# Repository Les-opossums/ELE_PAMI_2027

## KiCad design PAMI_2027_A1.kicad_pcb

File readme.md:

# ⚡ **PAMI_2027_A1** - KiCad Project

## 🌟 **Overview**

This repository contains the hardware design files for the **PAMI_2027_A1** PCB (Rev A1), designed using **KiCad 10**.

The board serves as the core control and power unit for the PAMI robot, built around the **RP2350A** microcontroller. Key features include:
- **Power Management:** Power rails providing 3.3V, 5V, 5V_SW, and 12V_VMOT. Powered by a wide-input battery stage supporting 6V to 9V+ operation with reverse-polarity protection and ideal diode controllers.
- **Triple Stepper Motor Control:** Driven by dedicated **TMC2209-LA** drivers with UART communication config.
- **Servo Motor Control:** Feetech or classic PWM servo control.
- **Sensor & Camera Expansion:** Integrated I2C camera multiplexer (`PCA9548ARGE`), LIDAR UART interface, OTOS sensor interface, EYE board interface.
- **HMI & Discrete Inputs:** Button inputs (`DSI_ON`, `DSI_STOP`, `DSI_CORD`, `DSI_TEAM`).
- **And more!:** USB programming, integrated memory, addressable RGB LED and debug interface.
- **Dimensions:** All in a 65 x 65 mm board !

---

## 🤖 **Hardware Design & Resources**

The hardware was designed using **KiCad 10.0.1**[cite: 3]. 

### **Schematic Sheets Structure**
* **`0100_MCU.kicad_sch`**: Microcontroller core (RP2350A, W25Q128 external flash, decoupling, and header breakouts).
* **`0200_Motors.kicad_sch`**: Triple TMC2209 stepper motor driver stages (`Motor1`, `Motor2`, `Motor3`).
* **`0300_I2C_CAM.kicad_sch`**: PCA9548ARGE I2C bus switch/multiplexer for multi-camera management.
* **`0400_IOEXT.kicad_sch`**: I/O adaptation stage, LM393 button inputs, and WS2812B RGB LED driver[cite: 6].
* **`0500_Power.kicad_sch`**: Power architecture featuring LM73100 ideal diodes, MPM3630 5V regulator, TPS61088 12V boost converter, and TLV76733 3.3V LDO.

---

## 📌 **RP2350A Pin Assignment & Peripherals**

The following table details the pin assignments on the main **RP2350A MCU** for onboard subsystems and external peripherals[cite: 4].

| GPIO | Function / Subsystem | Signal Name | Description |
| :---: | :---: | :---: | :--- |
| **GPIO 0** | Motor | `M3_STEP` | Motor 3 Step Control[cite: 4] |
| **GPIO 1** | Motor | `M3_DIR` | Motor 3 Direction Control[cite: 4] |
| **GPIO 2** | Sensor (I2C1) | `I2C_OTOS_SDA` / `12C1_SDA` | I2C Data for Odometry/Sensors[cite: 4] |
| **GPIO 3** | Sensor (I2C1) | `I2C_OTOS_SCL` / `12C1_SCL` | I2C Clock for Odometry/Sensors[cite: 4] |
| **GPIO 5** | Sensor (UART0) | `LIDAR_UART_TX` | UART Receive from LIDAR[cite: 4] |
| **GPIO 7** | HMI / Input | `DSI_STOP` | Display System Interface Stop signal[cite: 4] |
| **GPIO 8** | Motor | `M1_DIR` | Motor 1 Direction Control[cite: 4] |
| **GPIO 9** | HMI / Input | `DSI_CORD` | DSI Cord signal[cite: 4] |
| **GPIO 10** | HMI / Input | `DSI_TEAM` | DSI Team signal[cite: 4] |
| **GPIO 11** | Motor / Diagnostic | `M_nEN` | Global Motor Driver Enable (Active Low)[cite: 4] |
| **GPIO 12** | Motor | `M2_DIR` | Motor 2 Direction Control[cite: 4] |
| **GPIO 13** | UART / Motor | `MOT_UART_TX` | TMC2209 Steppers UART Transmit[cite: 4] |
| **GPIO 14** | UART / Motor | `MOT_UART_RX` | TMC2209 Steppers UART Receive[cite: 4] |
| **GPIO 16** | I2C0 (CAM) | `I2C_CAM_SDA` | I2C Data for Camera Multiplexer (PCA9548)[cite: 4] |
| **GPIO 17** | I2C0 (CAM) | `I2C_CAM_SCL` | I2C Clock for Camera Multiplexer (PCA9548)[cite: 4] |
| **GPIO 19** | Motor | `M3_STEP` (Alt) / PWM | Motor 3 Step / PWM[cite: 4] |
| **GPIO 22** | Motor | `M1_STEP` | Motor 1 Step Control[cite: 4] |
| **GPIO 26 (ADC0)** | Monitoring | `VBAT_MEAS` | Battery Voltage Measurement (Scaled ADC)[cite: 4] |
| **GPIO 27 (ADC1)** | Monitoring | `PAMI_MEAS` | Current/System Measurement ADC[cite: 4] |
| **GPIO 28** | PWM / Output | `PWM_S1` | Signal 1 PWM Output[cite: 4] |
| **GPIO 29** | PWM / Output | `PWM_LED` | RGB LED / Status PWM Output[cite: 4] |

---
## 📸 **Photos**

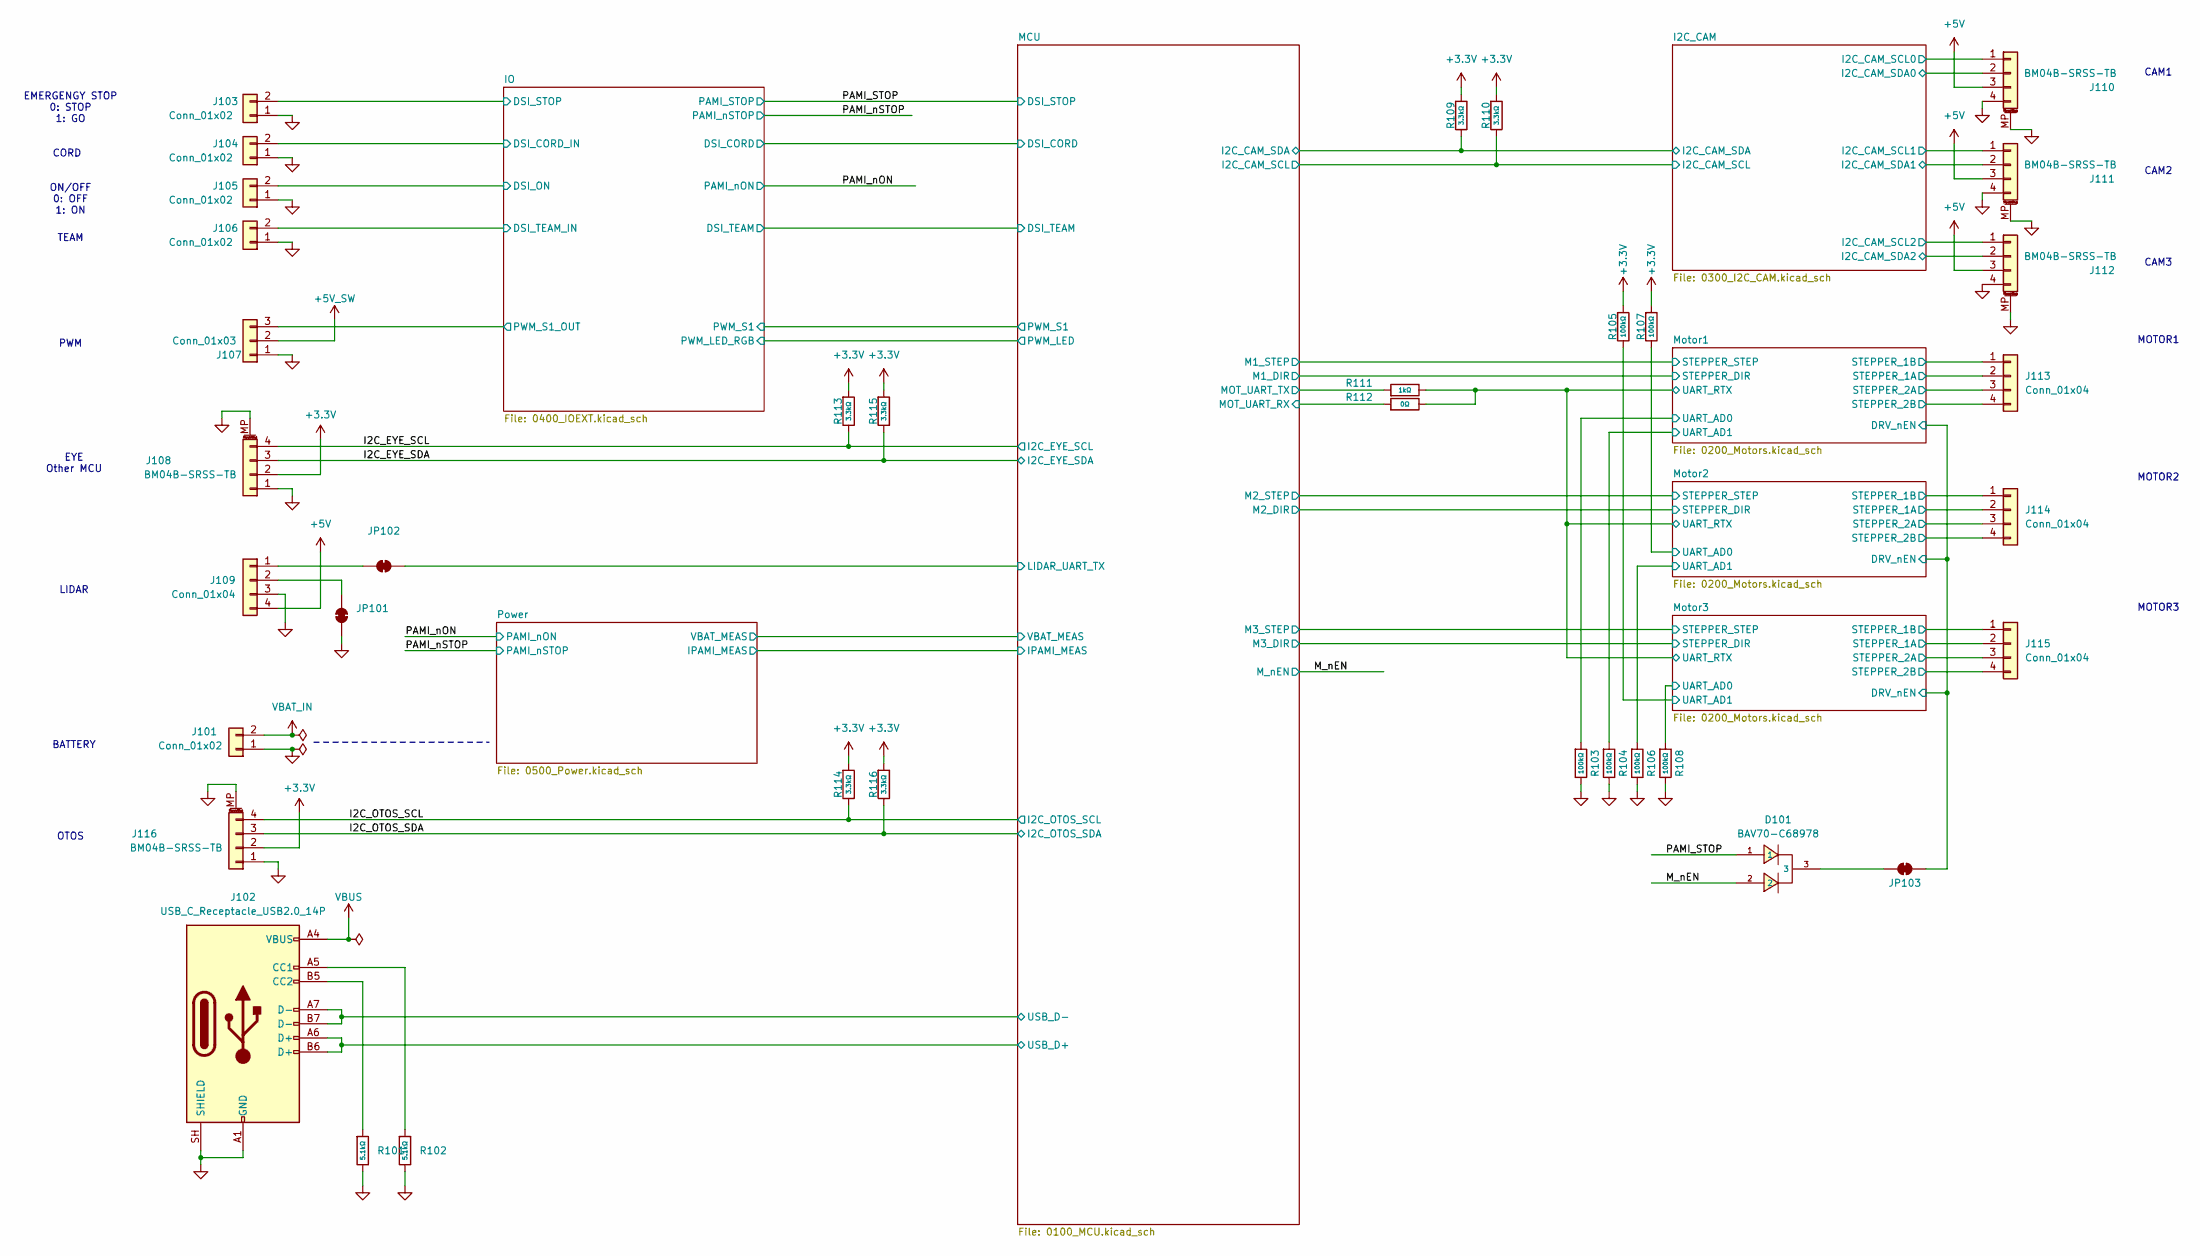
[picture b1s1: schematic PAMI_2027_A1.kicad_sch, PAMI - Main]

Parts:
D101: BAV70-C68978; SOT-23-3_L3.0-W1.7-P0.95-LS2.9-BR; Reverse Voltage (Vr) 70V; Forward Voltage (Vf@If) 1.25V@150mA; Part BAV70; LCSC C68978
J101: Conn_01x02; AMASS_XT30U-F_1x02_P5.0mm_Vertical
J102: USB_C_Receptacle_USB2.0_14P; USB_C_Receptacle_GCT_USB4105-xx-A_16P_TopMnt_Horizontal
J103, J104, J105, J106: Conn_01x02; JST_XH_B2B-XH-A_1x02_P2.50mm_Vertical
J107: Conn_01x03; JST_XH_B3B-XH-A_1x03_P2.50mm_Vertical
J108, J110, J111, J112, J116: BM04B-SRSS-TB; JST_SH_BM04B-SRSS-TB_1x04-1MP_P1.00mm_Vertical; JLCPCB Part # C160390
J109, J113, J114, J115: Conn_01x04; JST_XH_B4B-XH-A_1x04_P2.50mm_Vertical
JP101, JP102, JP103: SolderJumper_2_Bridged; SolderJumper-2_P1.3mm_Bridged_RoundedPad1.0x1.5mm
R101, R102: 5.1kΩ; R_0402; Overload Voltage (Max) 50V; Tolerance ±1%; Part 0402WGF5101TCE; LCSC C25905
R103, R104, R105, R106, R107, R108: 100kΩ; R_0402; Overload Voltage (Max) 50V; Tolerance ±1%; Part 0402WGF1003TCE; LCSC C25741
R109, R110, R113, R114, R115, R116: 3.3kΩ; R_0402; Overload Voltage (Max) 50V; Tolerance ±1%; Part 0402WGF3301TCE; LCSC C25890
R111: 1kΩ; R_0402; Overload Voltage (Max) 50V; Tolerance ±1%; Part 0402WGF1001TCE; LCSC C11702
R112: 0Ω; R_0402; Overload Voltage (Max) 50V; Tolerance ±1%; Part 0402WGF0000TCE; LCSC C17168

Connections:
+3.3V: J108.2, J116.2, R105.1, R107.1, R109.1, R110.1, R113.1, R114.1, R115.1, R116.1; also elsewhere on the board
+5V: J109.4, J110.3, J111.3, J112.3; also elsewhere on the board
+5V_SW: J107.2; also elsewhere on the board
/I2C_CAM/I2C_CAM_SCL0: J110.1; also elsewhere on the board
/I2C_CAM/I2C_CAM_SCL1: J111.1; also elsewhere on the board
/I2C_CAM/I2C_CAM_SCL2: J112.1; also elsewhere on the board
/I2C_CAM/I2C_CAM_SDA0: J110.2; also elsewhere on the board
/I2C_CAM/I2C_CAM_SDA1: J111.2; also elsewhere on the board
/I2C_CAM/I2C_CAM_SDA2: J112.2; also elsewhere on the board
/I2C_EYE_SCL: J108.4, R113.2; also elsewhere on the board
/I2C_EYE_SDA: J108.3, R115.2; also elsewhere on the board
/I2C_OTOS_SCL: J116.4, R114.2; also elsewhere on the board
/I2C_OTOS_SDA: J116.3, R116.2; also elsewhere on the board
/IO/DSI_CORD_IN: J104.2; also elsewhere on the board
/IO/DSI_ON: J105.2; also elsewhere on the board
/IO/DSI_STOP: J103.2; also elsewhere on the board
/IO/DSI_TEAM_IN: J106.2; also elsewhere on the board
/IO/PWM_S1_OUT: J107.3; also elsewhere on the board
/MCU/I2C_CAM_SCL: R110.2; also elsewhere on the board
/MCU/I2C_CAM_SDA: R109.2; also elsewhere on the board
/MCU/LIDAR_UART_TX: JP102.1 (A); also elsewhere on the board
/MCU/MOT_UART_RX: R112.1; also elsewhere on the board
/MCU/MOT_UART_TX: R111.1; also elsewhere on the board
/MCU/USB_D+: J102.A6 (D+), J102.B6 (D+); also elsewhere on the board
/MCU/USB_D-: J102.A7 (D-), J102.B7 (D-); also elsewhere on the board
/M_nEN: D101.2; also elsewhere on the board
/Motor1/DRV_nEN: JP103.1 (A); also elsewhere on the board
/Motor1/STEPPER_1A: J113.2; also elsewhere on the board
/Motor1/STEPPER_1B: J113.1; also elsewhere on the board
/Motor1/STEPPER_2A: J113.3; also elsewhere on the board
/Motor1/STEPPER_2B: J113.4; also elsewhere on the board
/Motor1/UART_AD0: R103.1; also elsewhere on the board
/Motor1/UART_AD1: R104.1; also elsewhere on the board
/Motor1/UART_RTX: R111.2, R112.2; also elsewhere on the board
/Motor2/STEPPER_1A: J114.2; also elsewhere on the board
/Motor2/STEPPER_1B: J114.1; also elsewhere on the board
/Motor2/STEPPER_2A: J114.3; also elsewhere on the board
/Motor2/STEPPER_2B: J114.4; also elsewhere on the board
/Motor2/UART_AD0: R107.2; also elsewhere on the board
/Motor2/UART_AD1: R106.1; also elsewhere on the board
/Motor3/STEPPER_1A: J115.2; also elsewhere on the board
/Motor3/STEPPER_1B: J115.1; also elsewhere on the board
/Motor3/STEPPER_2A: J115.3; also elsewhere on the board
/Motor3/STEPPER_2B: J115.4; also elsewhere on the board
/Motor3/UART_AD0: R108.1; also elsewhere on the board
/Motor3/UART_AD1: R105.2; also elsewhere on the board
/PAMI_STOP: D101.1; also elsewhere on the board
GND: J101.1, J102.A1 (GND), J102.A12 (GND), J102.B1 (GND), J102.B12 (GND), J102.SH (SHIELD), J103.1, J104.1, J105.1, J106.1, J107.1, J108.1, J108.MP (MountPin), J109.3, J110.4, J110.MP (MountPin), J111.4, J111.MP (MountPin), J112.4, J112.MP (MountPin), J116.1, J116.MP (MountPin), JP101.1 (A), R101.2, R102.2, R103.2, R104.2, R106.2, R108.2; also elsewhere on the board
unnamed: J102.A5 (CC1), R102.1
unnamed: J102.B5 (CC2), R101.1
unnamed: J109.1, JP102.2 (B)
unnamed: J109.2, JP101.2 (B)
unnamed: D101.3, JP103.2 (B)
VBAT_IN: J101.2; also elsewhere on the board
VBUS: J102.A4 (VBUS), J102.A9 (VBUS), J102.B4 (VBUS), J102.B9 (VBUS); also elsewhere on the board

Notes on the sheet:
ON/OFF 0: OFF 1: ON
OTOS
MOTOR2
PWM
BATTERY
EMERGENGY STOP 0: STOP 1: GO
CAM3
EYE Other MCU
MOTOR3
CAM2
LIDAR
CORD
MOTOR1
CAM1
TEAM

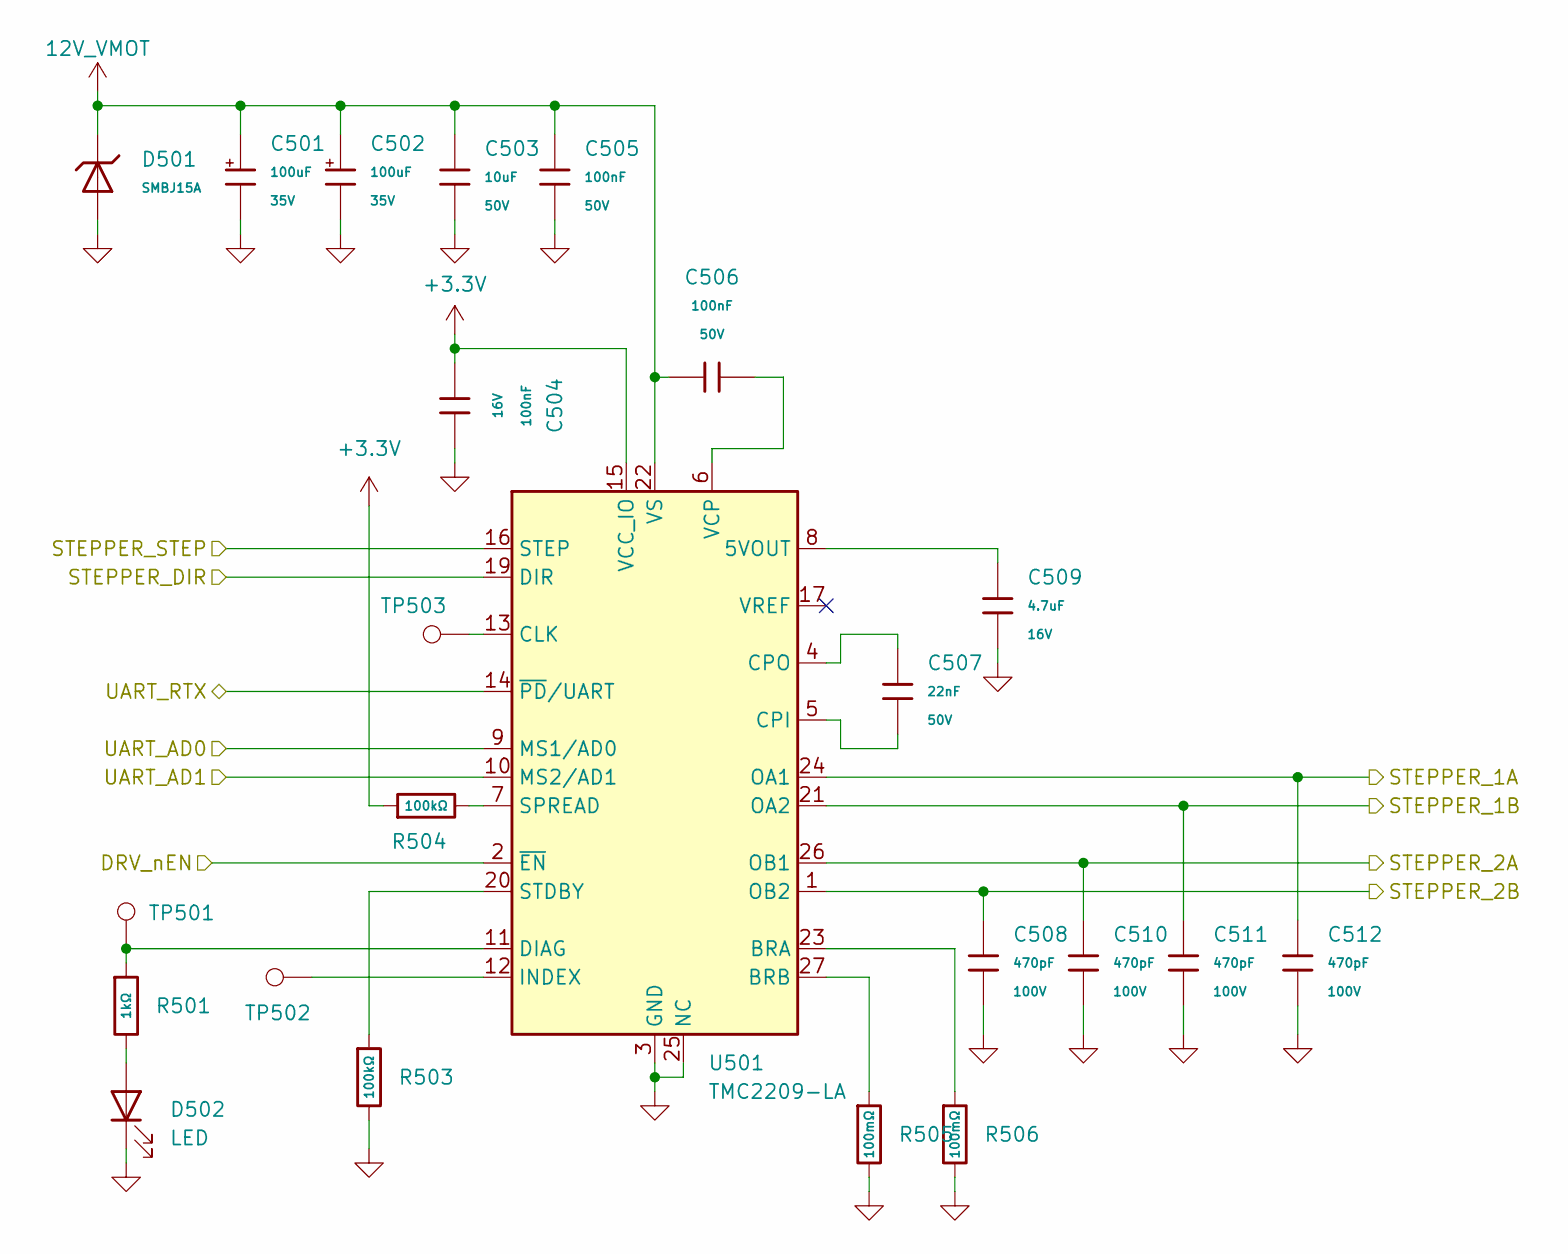
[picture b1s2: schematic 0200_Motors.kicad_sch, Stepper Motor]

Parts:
C501, C502: 100uF; CP_Elec_6.3x7.7; Tolerance ±10%; Rated Voltage 35V; Part RVT1V101M0607; LCSC C3339
C503: 10uF; C_0805; Voltage Rated 50V; Tolerance ±10%; Part GRM21BR61H106KE43L; LCSC C440198
C504: 100nF; C_0402; Voltage Rated 16V; Tolerance ±10%; Part CL05B104KO5NNNC; LCSC C1525
C505, C506: 100nF; C_0603; Voltage Rated 50V; Tolerance ±10%; Part CC0603KRX7R9BB104; LCSC C14663
C507: 22nF; C_0603; Voltage Rated 50V; Tolerance ±10%; Part CL10B223KB8NNNC; LCSC C21122
C508, C510, C511, C512: 470pF; C_0603; Voltage Rated 100V; Tolerance ±10%; Part 0603B471K101NT; LCSC C43255
C509: 4.7uF; C_0603; Voltage Rated 16V; Tolerance ±10%; Part CL10A475KO8NNNC; LCSC C19666
D501: SMBJ15A; D_SMB; Part SMBJ15A; LCSC C19077569
D502: LED; LED_0603_1608Metric_Pad1.05x0.95mm_HandSolder
R501: 1kΩ; R_0402; Overload Voltage (Max) 50V; Tolerance ±1%; Part 0402WGF1001TCE; LCSC C11702
R503, R504: 100kΩ; R_0402; Overload Voltage (Max) 50V; Tolerance ±1%; Part 0402WGF1003TCE; LCSC C25741
R505, R506: 100mΩ; R_1206; Overload Voltage (Max) 200V; Tolerance ±1%; Part HP06W2F100LT5E; LCSC C414960
TP501, TP502, TP503: TestPoint; TestPoint_Pad_D1.0mm
U501: TMC2209-LA; VQFN-28-1EP_5x5mm_P0.5mm_EP3.7x3.7mm_ThermalVias

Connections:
12V_VMOT: C501.1, C502.1, C503.1, C505.1, C506.1, D501.1, U501.22 (VS), U501.28 (VS); also elsewhere on the board
+3.3V: C504.1, R504.1, U501.15 (VCC_IO); also elsewhere on the board
/MCU/M1_DIR: U501.19 (DIR); also elsewhere on the board
/MCU/M1_STEP: U501.16 (STEP); also elsewhere on the board
/Motor1/DRV_nEN: U501.2 (~EN); also elsewhere on the board
/Motor1/STEPPER_1A: C512.1, U501.24 (OA1); also elsewhere on the board
/Motor1/STEPPER_1B: C511.1, U501.21 (OA2); also elsewhere on the board
/Motor1/STEPPER_2A: C510.1, U501.26 (OB1); also elsewhere on the board
/Motor1/STEPPER_2B: C508.1, U501.1 (OB2); also elsewhere on the board
/Motor1/UART_AD0: U501.9 (MS1/AD0); also elsewhere on the board
/Motor1/UART_AD1: U501.10 (MS2/AD1); also elsewhere on the board
/Motor1/UART_RTX: U501.14 (~PD/UART); also elsewhere on the board
GND: C501.2, C502.2, C503.2, C504.2, C505.2, C508.2, C509.2, C510.2, C511.2, C512.2, D501.2, D502.1 (K), R503.2, R505.2, R506.2, U501.3 (GND), U501.18 (GND), U501.25 (NC), U501.29 (GND); also elsewhere on the board
unnamed: D502.2 (A), R501.2
unnamed: C509.1, U501.8 (5VOUT)
unnamed: R506.1, U501.23 (BRA)
unnamed: R505.1, U501.27 (BRB)
unnamed: TP503.1 (1_1), U501.13 (CLK)
unnamed: C507.2, U501.5 (CPI)
unnamed: C507.1, U501.4 (CPO)
unnamed: R501.1, TP501.1 (1_1), U501.11 (DIAG)
unnamed: TP502.1 (1_1), U501.12 (INDEX)
unnamed: R504.2, U501.7 (SPREAD)
unnamed: R503.1, U501.20 (STDBY)
unnamed: C506.2, U501.6 (VCP)

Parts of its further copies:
C601, C602, C701, C702: 100uF; CP_Elec_6.3x7.7; Tolerance ±10%; Rated Voltage 35V; Part RVT1V101M0607; LCSC C3339
C603, C703: 10uF; C_0805; Voltage Rated 50V; Tolerance ±10%; Part GRM21BR61H106KE43L; LCSC C440198
C604, C704: 100nF; C_0402; Voltage Rated 16V; Tolerance ±10%; Part CL05B104KO5NNNC; LCSC C1525
C605, C606, C705, C706: 100nF; C_0603; Voltage Rated 50V; Tolerance ±10%; Part CC0603KRX7R9BB104; LCSC C14663
C607, C707: 22nF; C_0603; Voltage Rated 50V; Tolerance ±10%; Part CL10B223KB8NNNC; LCSC C21122
C608, C610, C611, C612, C708, C710, C711, C712: 470pF; C_0603; Voltage Rated 100V; Tolerance ±10%; Part 0603B471K101NT; LCSC C43255
C609, C709: 4.7uF; C_0603; Voltage Rated 16V; Tolerance ±10%; Part CL10A475KO8NNNC; LCSC C19666
D601, D701: SMBJ15A; D_SMB; Part SMBJ15A; LCSC C19077569
D602, D702: LED; LED_0603_1608Metric_Pad1.05x0.95mm_HandSolder
R601, R701: 1kΩ; R_0402; Overload Voltage (Max) 50V; Tolerance ±1%; Part 0402WGF1001TCE; LCSC C11702
R603, R604, R703, R704: 100kΩ; R_0402; Overload Voltage (Max) 50V; Tolerance ±1%; Part 0402WGF1003TCE; LCSC C25741
R605, R606, R705, R706: 100mΩ; R_1206; Overload Voltage (Max) 200V; Tolerance ±1%; Part HP06W2F100LT5E; LCSC C414960
TP601, TP602, TP603, TP701, TP702, TP703: TestPoint; TestPoint_Pad_D1.0mm
U601, U701: TMC2209-LA; VQFN-28-1EP_5x5mm_P0.5mm_EP3.7x3.7mm_ThermalVias

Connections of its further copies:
12V_VMOT: C601.1, C602.1, C603.1, C605.1, C606.1, C701.1, C702.1, C703.1, C705.1, C706.1, D601.1, D701.1, U601.22 (VS), U601.28 (VS), U701.22 (VS), U701.28 (VS); also elsewhere on the board
+3.3V: C604.1, C704.1, R604.1, R704.1, U601.15 (VCC_IO), U701.15 (VCC_IO); also elsewhere on the board
/MCU/M2_DIR: U601.19 (DIR); also elsewhere on the board
/MCU/M2_STEP: U601.16 (STEP); also elsewhere on the board
/MCU/M3_DIR: U701.19 (DIR); also elsewhere on the board
/MCU/M3_STEP: U701.16 (STEP); also elsewhere on the board
/Motor1/DRV_nEN: U601.2 (~EN), U701.2 (~EN); also elsewhere on the board
/Motor1/UART_RTX: U601.14 (~PD/UART), U701.14 (~PD/UART); also elsewhere on the board
/Motor2/STEPPER_1A: C612.1, U601.24 (OA1); also elsewhere on the board
/Motor2/STEPPER_1B: C611.1, U601.21 (OA2); also elsewhere on the board
/Motor2/STEPPER_2A: C610.1, U601.26 (OB1); also elsewhere on the board
/Motor2/STEPPER_2B: C608.1, U601.1 (OB2); also elsewhere on the board
/Motor2/UART_AD0: U601.9 (MS1/AD0); also elsewhere on the board
/Motor2/UART_AD1: U601.10 (MS2/AD1); also elsewhere on the board
/Motor3/STEPPER_1A: C712.1, U701.24 (OA1); also elsewhere on the board
/Motor3/STEPPER_1B: C711.1, U701.21 (OA2); also elsewhere on the board
/Motor3/STEPPER_2A: C710.1, U701.26 (OB1); also elsewhere on the board
/Motor3/STEPPER_2B: C708.1, U701.1 (OB2); also elsewhere on the board
/Motor3/UART_AD0: U701.9 (MS1/AD0); also elsewhere on the board
/Motor3/UART_AD1: U701.10 (MS2/AD1); also elsewhere on the board
GND: C601.2, C602.2, C603.2, C604.2, C605.2, C608.2, C609.2, C610.2, C611.2, C612.2, C701.2, C702.2, C703.2, C704.2, C705.2, C708.2, C709.2, C710.2, C711.2, C712.2, D601.2, D602.1 (K), D701.2, D702.1 (K), R603.2, R605.2, R606.2, R703.2, R705.2, R706.2, U601.3 (GND), U601.18 (GND), U601.25 (NC), U601.29 (GND), U701.3 (GND), U701.18 (GND), U701.25 (NC), U701.29 (GND); also elsewhere on the board
unnamed: D602.2 (A), R601.2
unnamed: D702.2 (A), R701.2
unnamed: C609.1, U601.8 (5VOUT)
unnamed: R606.1, U601.23 (BRA)
unnamed: R605.1, U601.27 (BRB)
unnamed: TP603.1 (1_1), U601.13 (CLK)
unnamed: C607.2, U601.5 (CPI)
unnamed: C607.1, U601.4 (CPO)
unnamed: R601.1, TP601.1 (1_1), U601.11 (DIAG)
unnamed: TP602.1 (1_1), U601.12 (INDEX)
unnamed: R604.2, U601.7 (SPREAD)
unnamed: R603.1, U601.20 (STDBY)
unnamed: C606.2, U601.6 (VCP)
unnamed: C709.1, U701.8 (5VOUT)
unnamed: R706.1, U701.23 (BRA)
unnamed: R705.1, U701.27 (BRB)
unnamed: TP703.1 (1_1), U701.13 (CLK)
unnamed: C707.2, U701.5 (CPI)
unnamed: C707.1, U701.4 (CPO)
unnamed: R701.1, TP701.1 (1_1), U701.11 (DIAG)
unnamed: TP702.1 (1_1), U701.12 (INDEX)
unnamed: R704.2, U701.7 (SPREAD)
unnamed: R703.1, U701.20 (STDBY)
unnamed: C706.2, U701.6 (VCP)

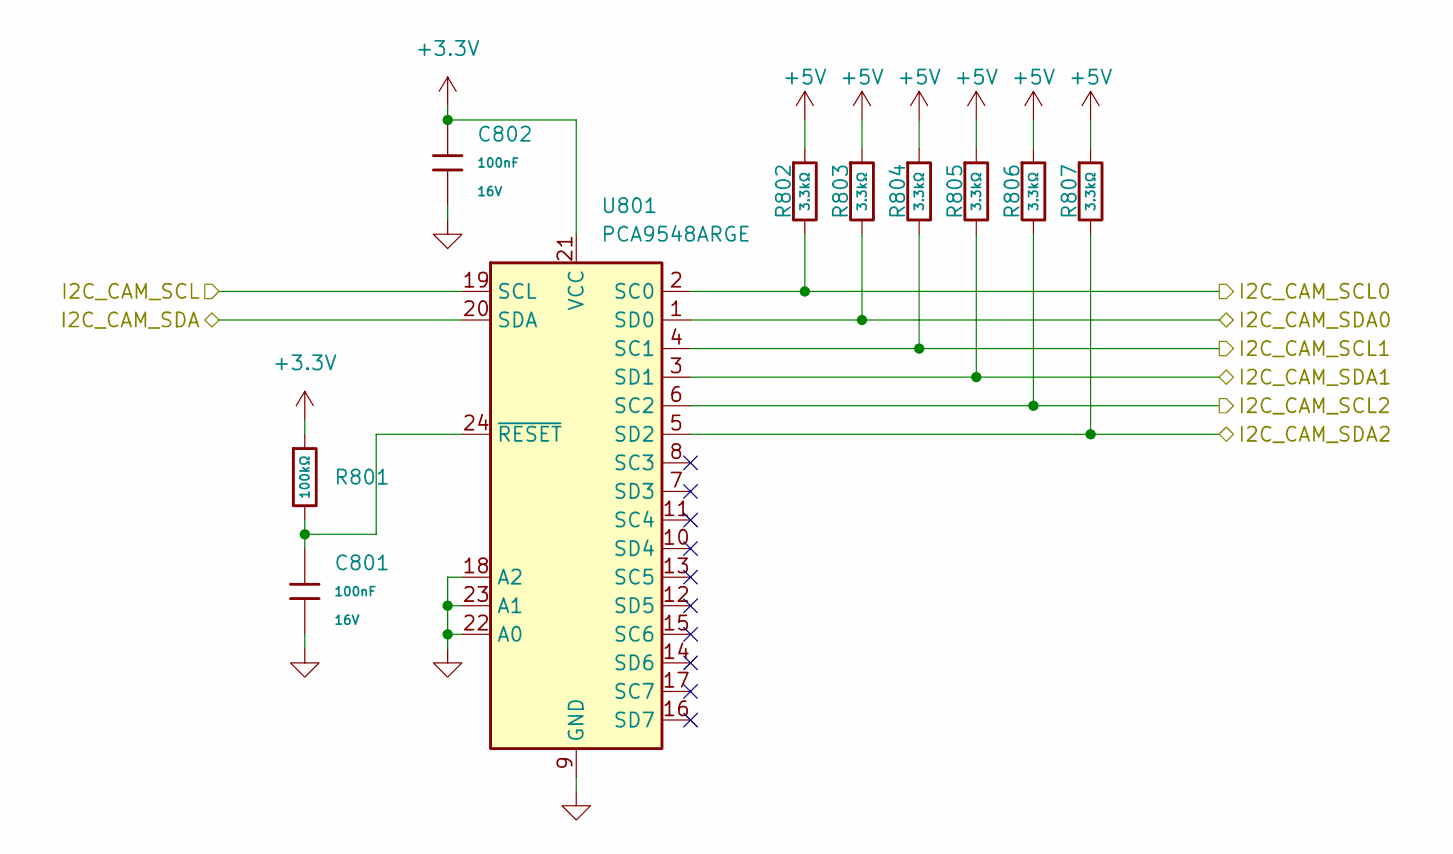
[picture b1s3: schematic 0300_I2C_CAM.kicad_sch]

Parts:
C801, C802: 100nF; C_0402; Voltage Rated 16V; Tolerance ±10%; Part CL05B104KO5NNNC; LCSC C1525
R801: 100kΩ; R_0402; Overload Voltage (Max) 50V; Tolerance ±1%; Part 0402WGF1003TCE; LCSC C25741
R802, R803, R804, R805, R806, R807: 3.3kΩ; R_0402; Overload Voltage (Max) 50V; Tolerance ±1%; Part 0402WGF3301TCE; LCSC C25890
U801: PCA9548ARGE; Texas_RGE0024C_VQFN-24-1EP_4x4mm_P0.5mm_EP2.1x2.1mm

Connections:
+3.3V: C802.2, R801.1, U801.21 (VCC); also elsewhere on the board
+5V: R802.1, R803.1, R804.1, R805.1, R806.1, R807.1; also elsewhere on the board
/I2C_CAM/I2C_CAM_SCL0: R802.2, U801.2 (SC0); also elsewhere on the board
/I2C_CAM/I2C_CAM_SCL1: R804.2, U801.4 (SC1); also elsewhere on the board
/I2C_CAM/I2C_CAM_SCL2: R806.2, U801.6 (SC2); also elsewhere on the board
/I2C_CAM/I2C_CAM_SDA0: R803.2, U801.1 (SD0); also elsewhere on the board
/I2C_CAM/I2C_CAM_SDA1: R805.2, U801.3 (SD1); also elsewhere on the board
/I2C_CAM/I2C_CAM_SDA2: R807.2, U801.5 (SD2); also elsewhere on the board
/MCU/I2C_CAM_SCL: U801.19 (SCL); also elsewhere on the board
/MCU/I2C_CAM_SDA: U801.20 (SDA); also elsewhere on the board
GND: C801.1, C802.1, U801.9 (GND), U801.18 (A2), U801.22 (A0), U801.23 (A1); also elsewhere on the board
unnamed: C801.2, R801.2, U801.24 (~RESET)

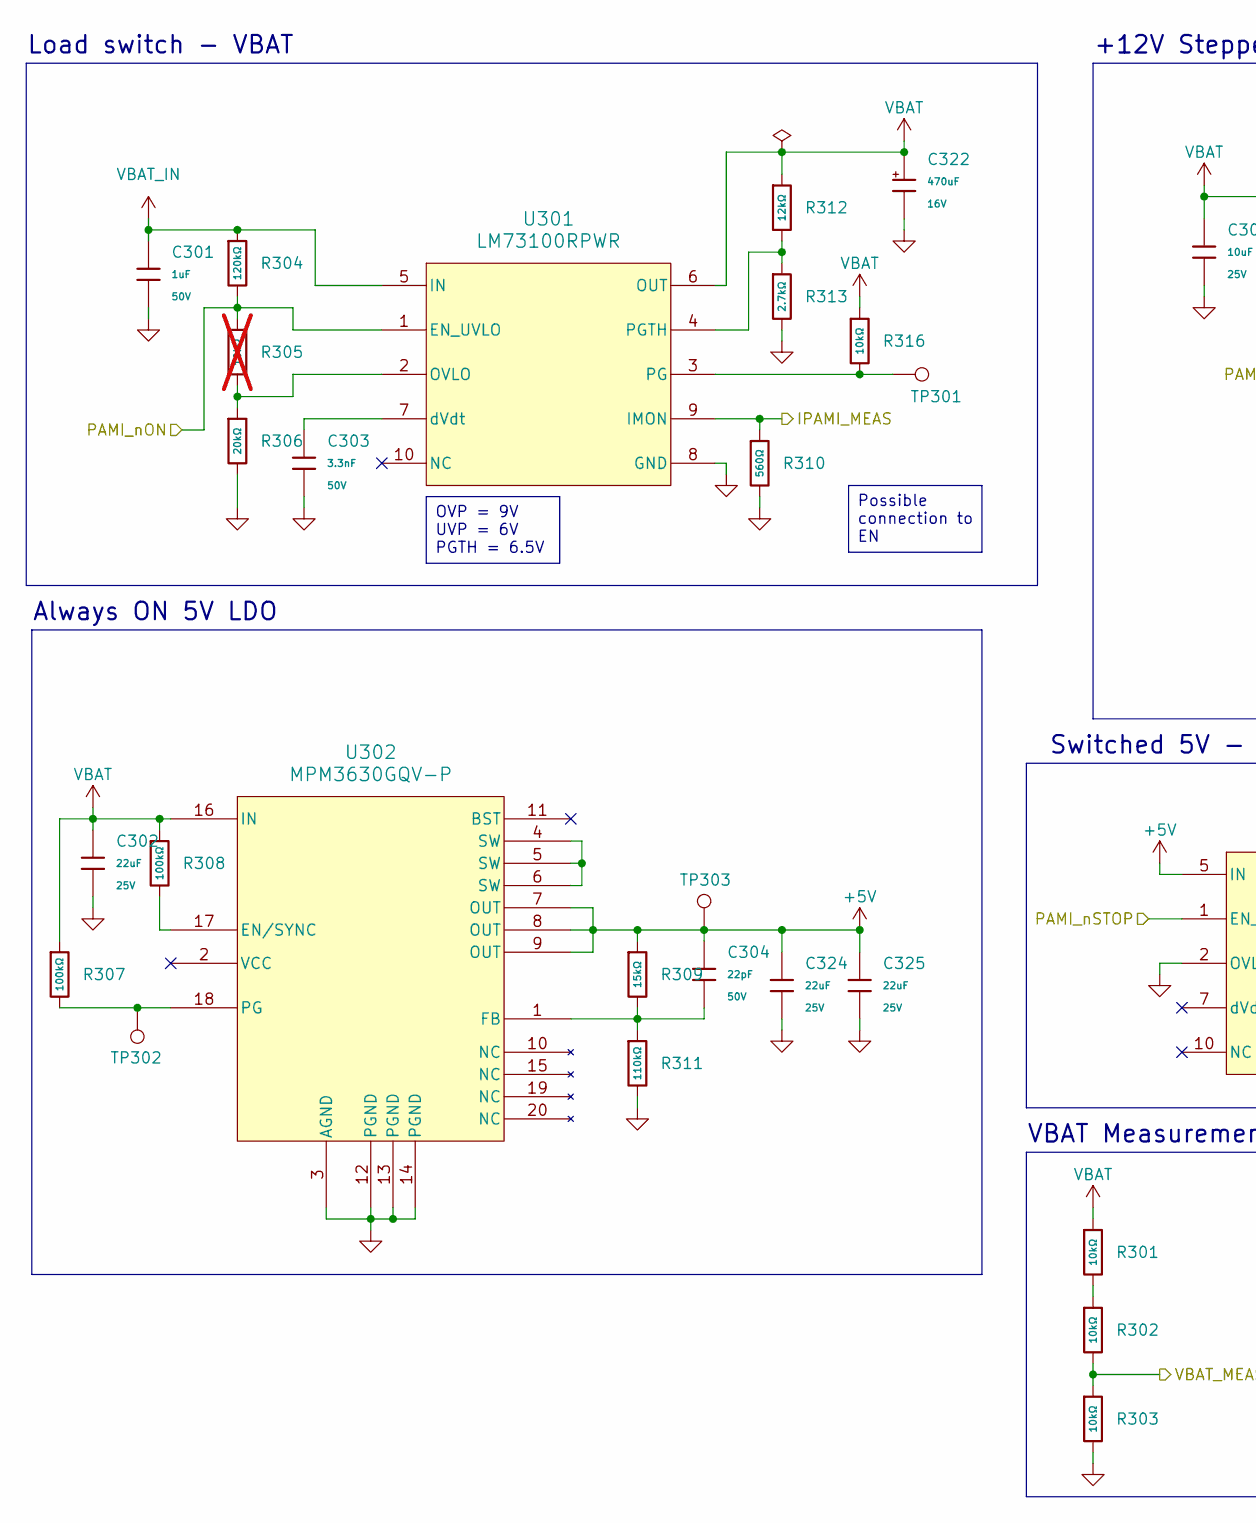
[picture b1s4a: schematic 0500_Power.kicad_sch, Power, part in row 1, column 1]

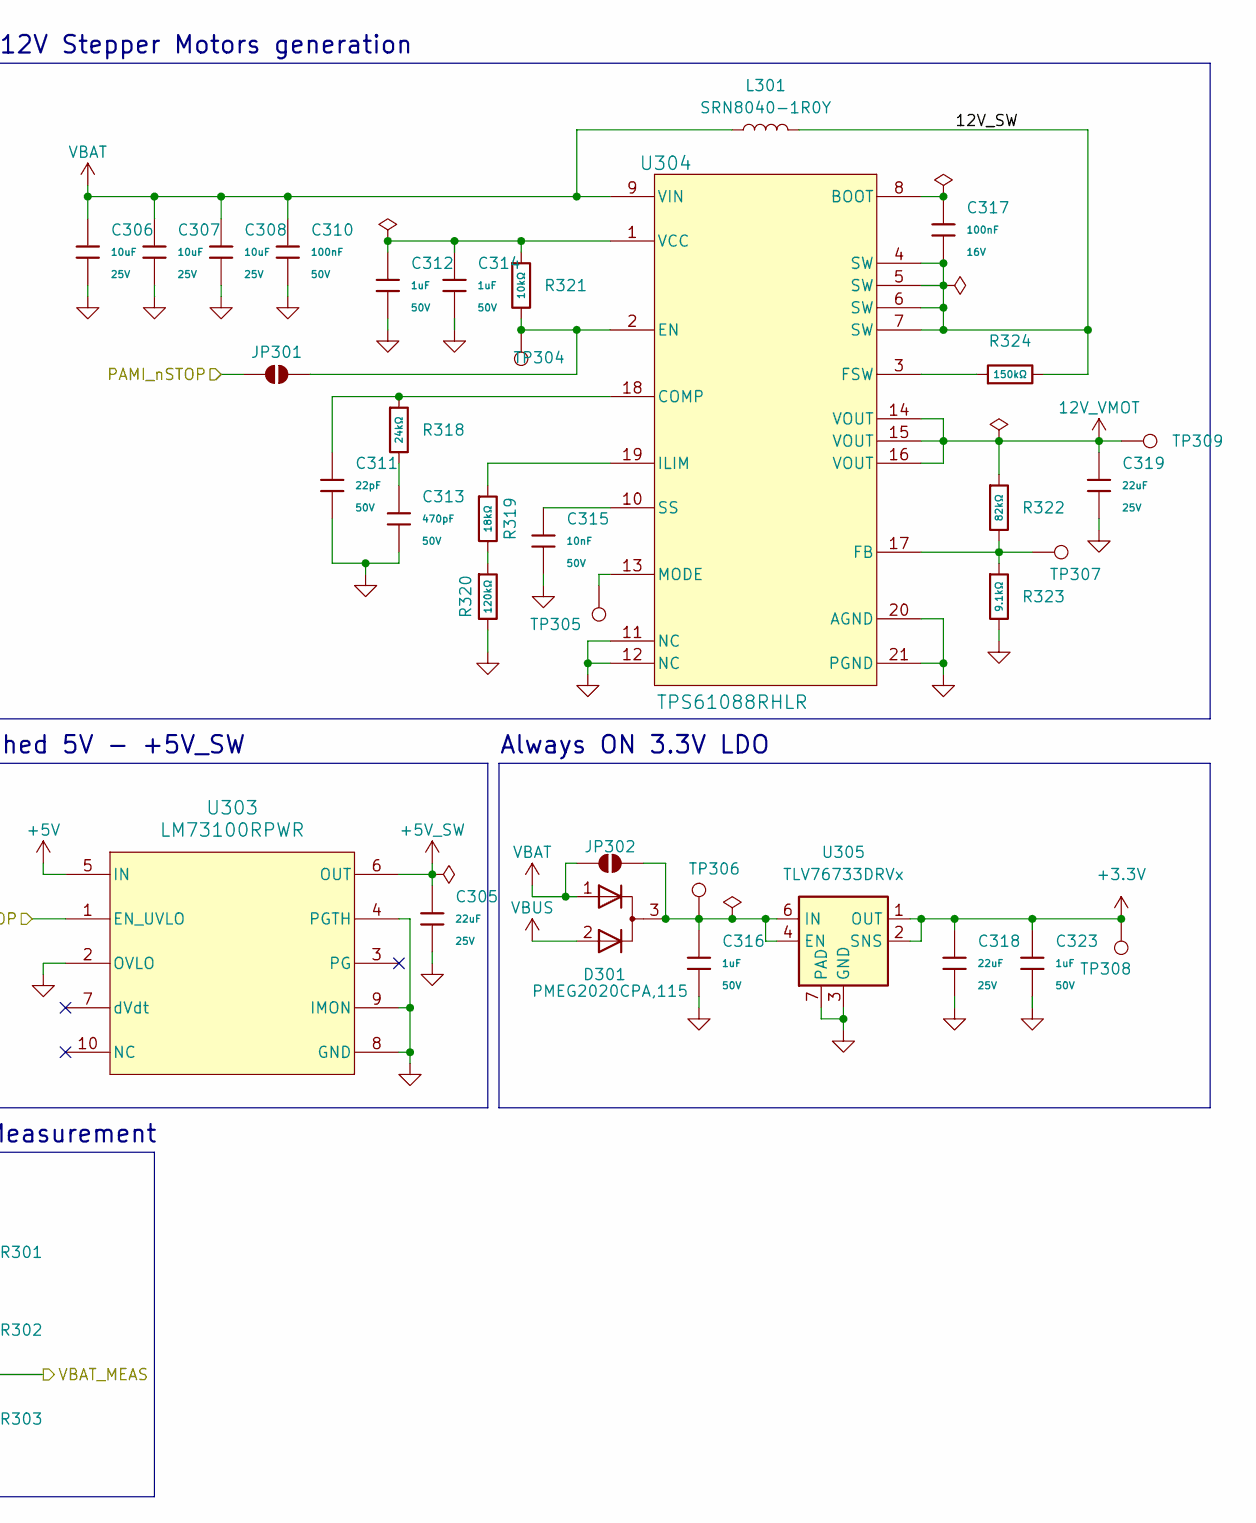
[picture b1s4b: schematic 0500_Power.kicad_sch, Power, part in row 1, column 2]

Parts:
C301, C312, C314, C316, C323: 1uF; C_0603; Voltage Rated 50V; Tolerance ±10%; Part CL10A105KB8NNNC; LCSC C15849
C302, C305, C318, C319, C324, C325: 22uF; C_0805; Voltage Rated 25V; Tolerance ±20%; Part CL21A226MAQNNNE; LCSC C45783
C303: 3.3nF; C_0402; Voltage Rated 50V; Tolerance ±10%; Part CL05B332KB5NNNC; LCSC C26404
C304, C311: 22pF; C_0402; Voltage Rated 50V; Tolerance ±5%; Part 0402CG220J500NT; LCSC C1555
C306, C307, C308: 10uF; C_0805; Voltage Rated 25V; Tolerance ±10%; Part CL21A106KAYNNNE; LCSC C15850
C310: 100nF; C_0603; Voltage Rated 50V; Tolerance ±10%; Part CC0603KRX7R9BB104; LCSC C14663
C313: 470pF; C_0402; Voltage Rated 50V; Tolerance ±10%; Part 0402B471K500NT; LCSC C1537
C315: 10nF; C_0402; Voltage Rated 50V; Tolerance ±10%; Part CL05B103KB5NNNC; LCSC C15195
C317: 100nF; C_0402; Voltage Rated 16V; Tolerance ±10%; Part CL05B104KO5NNNC; LCSC C1525
C322: 470uF; CP_Elec_8x10; Tolerance ±10%; Rated Voltage 16V; Part RVT1C471M0810; LCSC C3341
D301: PMEG2020CPA,115; HUSON-3-1EP_2x2mm_P1.3mm_EP1.1x1.6mm
JP301, JP302: SolderJumper_2_Open; SolderJumper-2_P1.3mm_Open_RoundedPad1.0x1.5mm
L301: SRN8040-1R0Y; L_Bourns-SRN8040_8x8.15mm
R301, R302, R303, R316, R321: 10kΩ; R_0402; Overload Voltage (Max) 50V; Tolerance ±1%; Part 0402WGF1002TCE; LCSC C25744
R304, R320: 120kΩ; R_0402; Overload Voltage (Max) 50V; Tolerance ±1%; Part 0402WGF1203TCE; LCSC C25750
R305: 10kΩ; R_0402; Overload Voltage (Max) 50V; Tolerance ±1%; Part 0402WGF1002TCE; LCSC C25744; not fitted
R306: 20kΩ; R_0402; Overload Voltage (Max) 50V; Tolerance ±1%; Part 0402WGF2002TCE; LCSC C25765
R307, R308: 100kΩ; R_0402; Overload Voltage (Max) 50V; Tolerance ±1%; Part 0402WGF1003TCE; LCSC C25741
R309: 15kΩ; R_0402; Overload Voltage (Max) 50V; Tolerance ±1%; Part 0402WGF1502TCE; LCSC C25756
R310: 560Ω; R_0603; Overload Voltage (Max) 75V; Tolerance ±1%; Part 0603WAF5600T5E; LCSC C23204
R311: 110kΩ; R_0402; Overload Voltage (Max) 50V; Tolerance ±1%; Part 0402WGF1103TCE; LCSC C25745
R312: 12kΩ; R_0402; Overload Voltage (Max) 50V; Tolerance ±1%; Part 0402WGF1202TCE; LCSC C25752
R313: 2.7kΩ; R_0603; Overload Voltage (Max) 75V; Tolerance ±1%; Part 0603WAF2701T5E; LCSC C13167
R318: 24kΩ; R_0402; Overload Voltage (Max) 50V; Tolerance ±1%; Part 0402WGF2402TCE; LCSC C25769
R319: 18kΩ; R_0402; Overload Voltage (Max) 50V; Tolerance ±1%; Part 0402WGF1802TCE; LCSC C25762
R322: 82kΩ; R_0603; Overload Voltage (Max) 75V; Tolerance ±1%; Part 0603WAF8202T5E; LCSC C23254
R323: 9.1kΩ; R_0603; Overload Voltage (Max) 75V; Tolerance ±1%; Part 0603WAF9101T5E; LCSC C23260
R324: 150kΩ; R_0402; Overload Voltage (Max) 50V; Tolerance ±1%; Part 0402WGF1503TCE; LCSC C25755
TP301, TP302, TP303, TP304, TP305, TP306, TP307, TP308, TP309: TestPoint; TestPoint_Pad_D1.0mm
U301, U303: LM73100RPWR; RPW0010A-MFG
U302: MPM3630GQV-P; MPM3630_MNP
U304: TPS61088RHLR; RHL0020A
U305: TLV76733DRVx; WSON-6-1EP_2x2mm_P0.65mm_EP1x1.6mm_ThermalVias

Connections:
12V_VMOT: C319.1, R322.1, TP309.1 (1_1), U304.14 (VOUT), U304.15 (VOUT), U304.16 (VOUT); also elsewhere on the board
+3.3V: C318.1, C323.1, TP308.1 (1_1), U305.1 (OUT), U305.2 (SNS); also elsewhere on the board
+5V: C304.1, C324.1, C325.1, R309.1, TP303.1 (1_1), U302.7 (OUT), U302.8 (OUT), U302.9 (OUT), U303.5 (IN); also elsewhere on the board
+5V_SW: C305.1, U303.6 (OUT); also elsewhere on the board
/MCU/IPAMI_MEAS: R310.1, U301.9 (IMON); also elsewhere on the board
/MCU/VBAT_MEAS: R302.2, R303.1; also elsewhere on the board
/PAMI_nON: R304.2, R305.1, U301.1 (EN_UVLO); also elsewhere on the board
/PAMI_nSTOP: JP301.1 (A), U303.1 (EN_UVLO); also elsewhere on the board
/Power/12V_SW: C317.1, L301.2, R324.2, U304.4 (SW), U304.5 (SW), U304.6 (SW), U304.7 (SW)
GND: C301.2, C302.2, C303.2, C305.2, C306.2, C307.2, C308.2, C310.2, C311.2, C312.2, C313.2, C314.2, C315.2, C316.2, C318.2, C319.2, C322.2, C323.2, C324.2, C325.2, R303.2, R306.2, R310.2, R311.2, R313.2, R320.2, R323.2, U301.8 (GND), U302.3 (AGND), U302.12 (PGND), U302.13 (PGND), U302.14 (PGND), U303.2 (OVLO), U303.4 (PGTH), U303.8 (GND), U303.9 (IMON), U304.11 (NC), U304.12 (NC), U304.20 (AGND), U304.21 (PGND), U305.3 (GND), U305.5 (GND), U305.7 (PAD); also elsewhere on the board
unnamed: C313.1, R318.2
unnamed: C316.1, D301.3 (K), JP302.2 (B), TP306.1 (1_1), U305.4 (EN), U305.6 (IN)
unnamed: JP301.2 (B), R321.2, TP304.1 (1_1), U304.2 (EN)
unnamed: R301.2, R302.1
unnamed: R319.2, R320.1
unnamed: R305.2, R306.1, U301.2 (OVLO)
unnamed: R316.2, TP301.1 (1_1), U301.3 (PG)
unnamed: R312.2, R313.1, U301.4 (PGTH)
unnamed: C303.1, U301.7 (dVdt)
unnamed: R308.2, U302.17 (EN/SYNC)
unnamed: C304.2, R309.2, R311.1, U302.1 (FB)
unnamed: R307.2, TP302.1 (1_1), U302.18 (PG)
unnamed: U302.4 (SW), U302.5 (SW), U302.6 (SW)
unnamed: C317.2, U304.8 (BOOT)
unnamed: C311.1, R318.1, U304.18 (COMP)
unnamed: R322.2, R323.1, TP307.1 (1_1), U304.17 (FB)
unnamed: R324.1, U304.3 (FSW)
unnamed: R319.1, U304.19 (ILIM)
unnamed: TP305.1 (1_1), U304.13 (MODE)
unnamed: C315.1, U304.10 (SS)
unnamed: C312.1, C314.1, R321.1, U304.1 (VCC)
VBAT: C302.1, C306.1, C307.1, C308.1, C310.1, C322.1, D301.1 (A), JP302.1 (A), L301.1, R301.1, R307.1, R308.1, R312.1, R316.1, U301.6 (OUT), U302.16 (IN), U304.9 (VIN); also elsewhere on the board
VBAT_IN: C301.1, R304.1, U301.5 (IN); also elsewhere on the board
VBUS: D301.2 (A); also elsewhere on the board

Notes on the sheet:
Always ON 5V LDO
VBAT Measurement
Load switch - VBAT
Always ON 3.3V LDO
+12V Stepper Motors generation
Switched 5V - +5V_SW
OVP = 9V UVP = 6V PGTH = 6.5V
Possible connection to EN
